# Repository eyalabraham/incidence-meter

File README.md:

# Incidence meter for RC planes

This project implements an incidence meter to measure airfoil angles on RC planes. The project uses an AVR ATMega328p, a set of seven segment LED modules, and an I2C accelerometer module.  Use to measure absolute of aerodynamic surface and relative angle between them.  Project includes code for AVR, schematic and Gerber files for circuit board, and CAD files for 3D printing of mechanical parts. 

## Using the meter

Assemble the circuit board and print the mechanical parts. Then assemble the meter as depicted here

<pic>

### Calibration 

Calibrate the meter before using for the first time and if using after long storage or changing mechanical parts. Calibration stores the zero angle error offset resulting from mechanical imperfections in the AVR EEPROM. 

1.	Stand the meter on a level surface, preferably one that was leveled with a separate leveling tool
2.	Turn on the meter.
3.	If the meter does not have stored calibration information then the calibration LED will blink continuously. You can still measure angles, but the measurements may not be accurate.
4.	Use a non-metal point tool to push the calibration button and check that the calibration LED turns on, or will stop blinking and stay on. 
5.	When ready, press the hold/zero button to store the calibration data. 
6.	The Calibration LED will turn off and the calibration LED should turn off indicating a valid calibration. 
7.	Calibration can be entered and repeated at any time as required. 

### Using the meter

The meter can be used to measure incidence angles on a plane’s aerodynamic surface (wing, stabilizer/elevator) or the relative angle between surfaces.

#### Surface angle

1.	Place the assembled air-frame on a leveled surface. Pre-level the surface with the meter (zero degree angle) or a different leveling tool. Level the surface in two directions at right angle to each other. 
2.	Clamp the meter to the surface. 
3.	Read the angle on the meter. 
4.	Note that this is the angle of incidence relative to the level surface; ground. 

#### Relative incidence angle

1.	Make sure ailerons and elevator are neutral. 
2.	Follow steps 1 through 3 above on the aircraft’s wing. 
3.	Press the Zero/Hold button 
4.	The display should read zero
5.	Move the meter and clamp to a different surface such as the horizontal stabilizer. 
6.	The reading on the meter now shows the relative incidence angle between horizontal stabilizer and wing. Positive or negative indicates a positive or negative incidence angle.
7.	Compare the measurement to the plans or manufacturer recommendations.

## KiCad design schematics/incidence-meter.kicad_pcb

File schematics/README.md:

# AVR ATMega328P incidence meter KiCAD schematic and PCB

This project implements an incidence meter to measure airfoil angles on RC planes. The project uses an AVR ATMega328p, a set of seven segment LED modules, and an I2C accelerometer module.

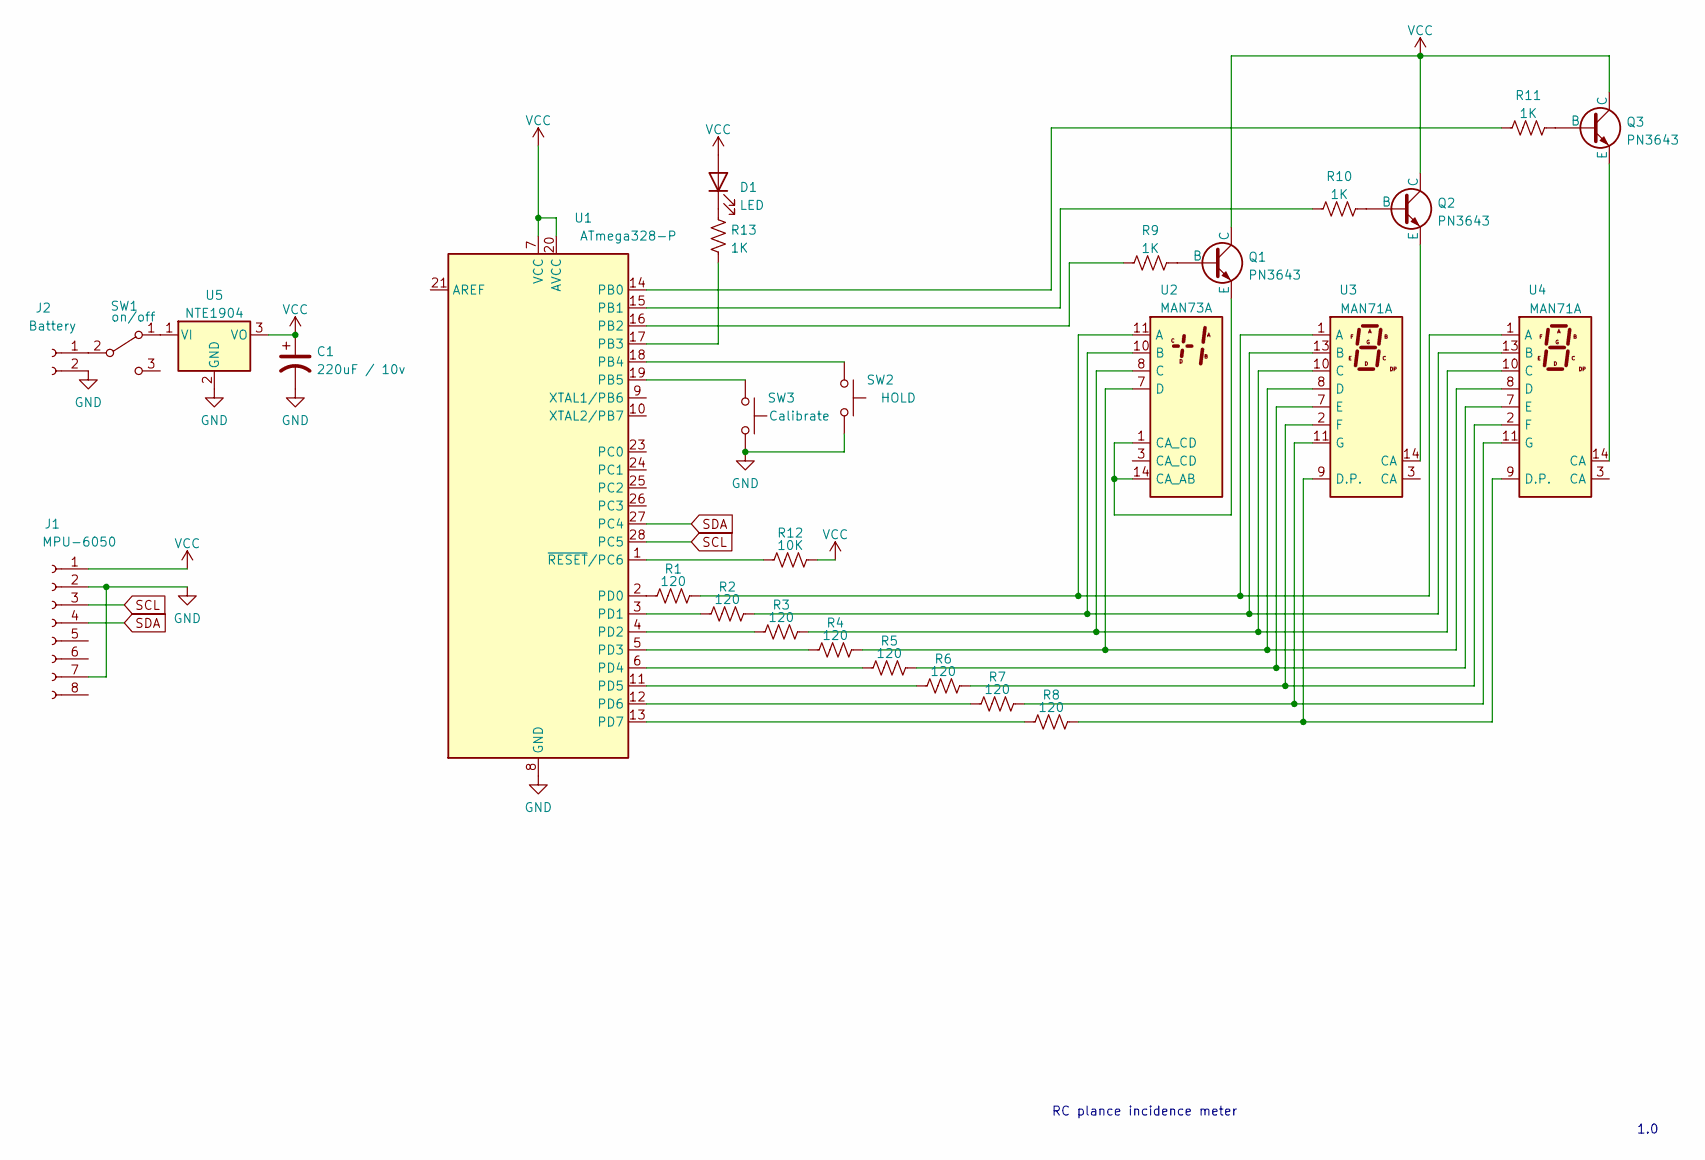
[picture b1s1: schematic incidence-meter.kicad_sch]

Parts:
C1: 220uF / 10v; CP_Radial_D6.3mm_P2.50mm
D1: LED; LED_D3.0mm
J1: MPU-6050; PinSocket_1x08_P2.54mm_Vertical
J2: Battery; PinHeader_1x02_P2.54mm_Vertical
Q1, Q2, Q3: PN3643; TO-92L_HandSolder
R1, R2, R3, R4, R5, R6, R7, R8: 120; R_Axial_DIN0207_L6.3mm_D2.5mm_P7.62mm_Horizontal
R9, R10, R11, R13: 1K; R_Axial_DIN0207_L6.3mm_D2.5mm_P7.62mm_Horizontal
R12: 10K; R_Axial_DIN0207_L6.3mm_D2.5mm_P7.62mm_Horizontal
SW1: on/off; SPDT_MINIATURE_SLIDE_SW_PHILMORE_30-9185
SW2: HOLD; SW_PUSH-12mm
SW3: Calibrate; SW_Tactile_Straight_KSA0Axx1LFTR
U1: ATmega328-P; DIP-28_W7.62mm
U2: MAN73A
U3, U4: MAN71A
U5: NTE1904; TO-220-3_Vertical

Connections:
GND: C1.2, J1.2, J1.7, J2.2, SW2.2, SW3.2, U1.8 (GND), U1.22 (GND), U5.2 (GND)
unnamed: D1.1 (K), R13.2
unnamed: J2.1, SW1.2 (B)
unnamed: Q1.1 (E), U2.1 (CA_CD), U2.14 (CA_AB)
unnamed: Q1.2 (B), R9.1
unnamed: Q2.1 (E), U3.14 (CA)
unnamed: Q2.2 (B), R10.1
unnamed: Q3.1 (E), U4.14 (CA)
unnamed: Q3.2 (B), R11.1
unnamed: R1.1, U2.11 (A), U3.1 (A), U4.1 (A)
unnamed: R1.2, U1.2 (PD0)
unnamed: R2.1, U2.10 (B), U3.13 (B), U4.13 (B)
unnamed: R2.2, U1.3 (PD1)
unnamed: R3.1, U2.8 (C), U3.10 (C), U4.10 (C)
unnamed: R3.2, U1.4 (PD2)
unnamed: R4.1, U2.7 (D), U3.8 (D), U4.8 (D)
unnamed: R4.2, U1.5 (PD3)
unnamed: R5.1, U3.7 (E), U4.7 (E)
unnamed: R5.2, U1.6 (PD4)
unnamed: R6.1, U3.2 (F), U4.2 (F)
unnamed: R6.2, U1.11 (PD5)
unnamed: R7.1, U3.11 (G), U4.11 (G)
unnamed: R7.2, U1.12 (PD6)
unnamed: R8.1, U3.9 (D.P.), U4.9 (D.P.)
unnamed: R8.2, U1.13 (PD7)
unnamed: R9.2, U1.16 (PB2)
unnamed: R10.2, U1.15 (PB1)
unnamed: R11.2, U1.14 (PB0)
unnamed: R12.2, U1.1 (~RESET/PC6)
unnamed: R13.1, U1.17 (PB3)
unnamed: SW1.1 (A), U5.1 (VI)
unnamed: SW2.1, U1.18 (PB4)
unnamed: SW3.1, U1.19 (PB5)
SCL: J1.3, U1.28 (PC5)
SDA: J1.4, U1.27 (PC4)
VCC: C1.1, D1.2 (A), J1.1, Q1.3 (C), Q2.3 (C), Q3.3 (C), R12.1, U1.7 (VCC), U1.20 (AVCC), U5.3 (VO)

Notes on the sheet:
1.0
RC plance incidence meter

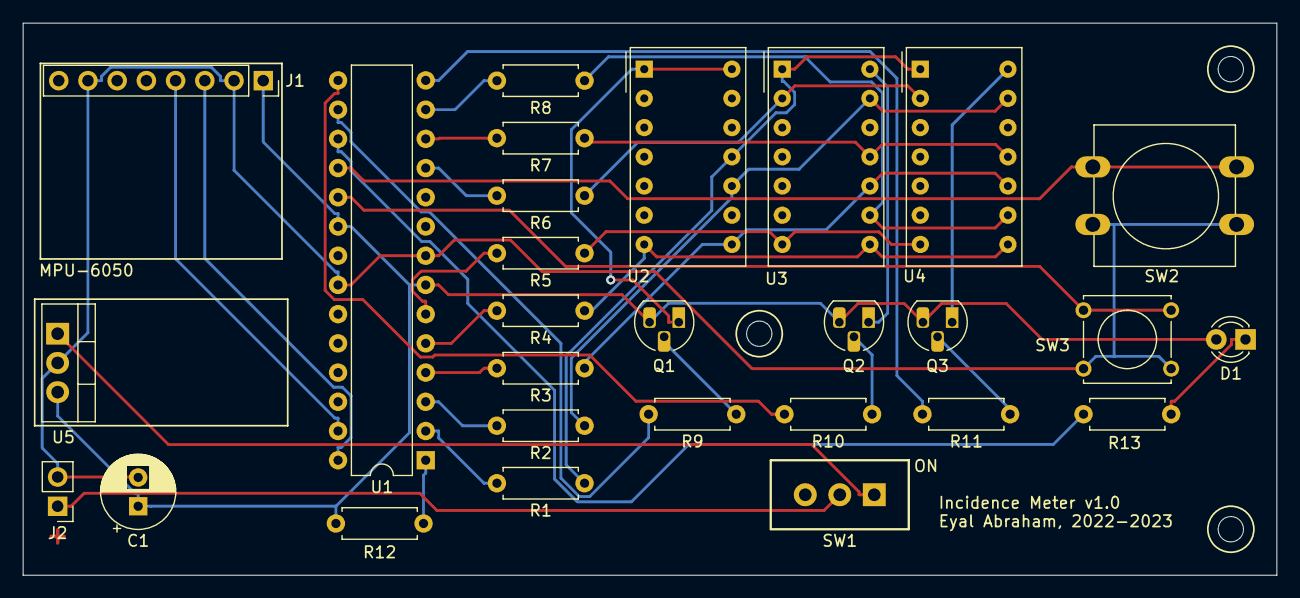
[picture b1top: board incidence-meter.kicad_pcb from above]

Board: 2 copper layers, 109.0 x 48.0 mm, 28 parts (0 on the bottom side), 36 nets.

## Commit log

2023-01-17 First commit.
